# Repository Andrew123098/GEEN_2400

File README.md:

# EngineeringForTheCommunity

A Particle project named EngineeringForTheCommunity

## Welcome to your project!

Every new Particle project is composed of 3 important elements that you'll see have been created in your project directory for EngineeringForTheCommunity.

#### ```/src``` folder:  
This is the source folder that contains the firmware files for your project. It should *not* be renamed. 
Anything that is in this folder when you compile your project will be sent to our compile service and compiled into a firmware binary for the Particle device that you have targeted.

If your application contains multiple files, they should all be included in the `src` folder. If your firmware depends on Particle libraries, those dependencies are specified in the `project.properties` file referenced below.

#### ```.ino``` file:
This file is the firmware that will run as the primary application on your Particle device. It contains a `setup()` and `loop()` function, and can be written in Wiring or C/C++. For more information about using the Particle firmware API to create firmware for your Particle device, refer to the [Firmware Reference](https://docs.particle.io/reference/firmware/) section of the Particle documentation.

#### ```project.properties``` file:  
This is the file that specifies the name and version number of the libraries that your project depends on. Dependencies are added automatically to your `project.properties` file when you add a library to a project using the `particle library add` command in the CLI or add a library in the Desktop IDE.

## Adding additional files to your project

#### Projects with multiple sources
If you would like add additional files to your application, they should be added to the `/src` folder. All files in the `/src` folder will be sent to the Particle Cloud to produce a compiled binary.

#### Projects with external libraries
If your project includes a library that has not been registered in the Particle libraries system, you should create a new folder named `/lib/<libraryname>/src` under `/<project dir>` and add the `.h` and `.cpp` files for your library there. All contents of the `/lib` folder and subfolders will also be sent to the Cloud for compilation.

## Compiling your project

When you're ready to compile your project, make sure you have the correct Particle device target selected and run `particle compile <platform>` in the CLI or click the Compile button in the Desktop IDE. The following files in your project folder will be sent to the compile service:

- Everything in the `/src` folder, including your `.ino` application file
- The `project.properties` file for your project
- Any libraries stored under `lib/<libraryname>/src`# GEEN_2400

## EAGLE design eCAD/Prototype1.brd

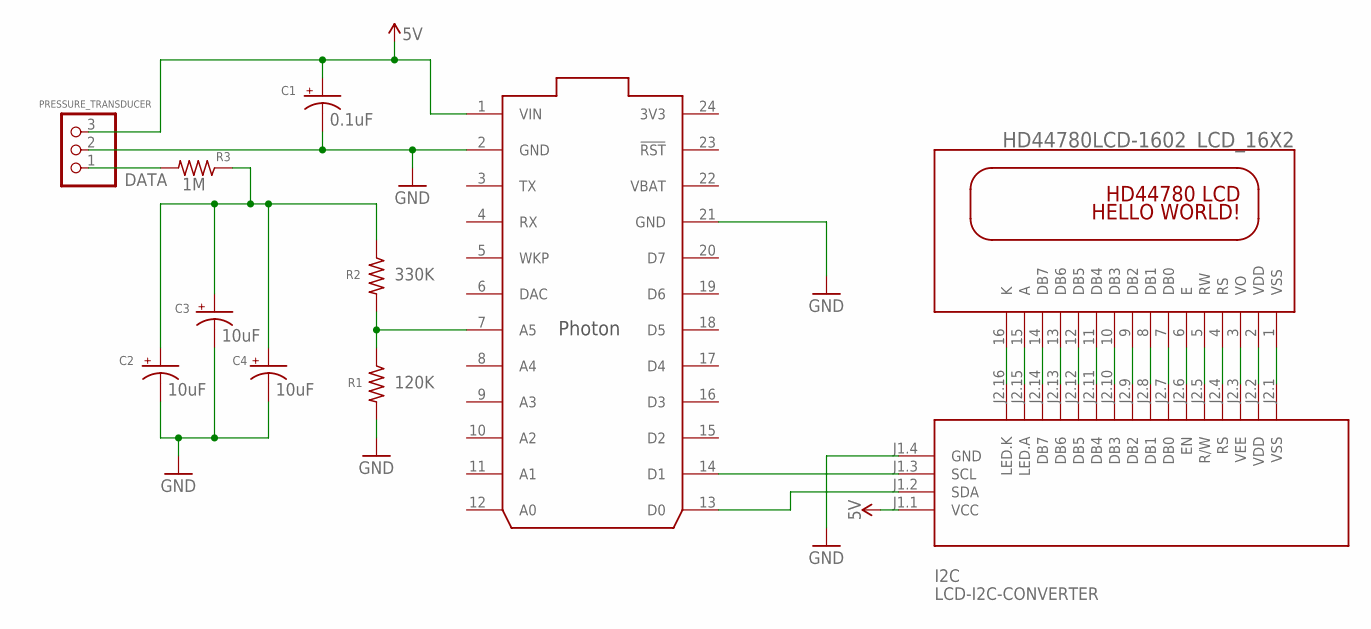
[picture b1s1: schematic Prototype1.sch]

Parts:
C1: 0.1uF; E2,5-7
C2, C3, C4: 10uF; E2,5-5
I2C: LCD-I2C-CONVERTER
LCD_16X2: HD44780LCD-1602; LCD1602
PHOTON: PHOTON_WITH_HEADERS; PHOTON
PRESSURE_TRANSDUCER: PINHD-1X3; 1X03
R1: 120K; 0207/10
R2: 330K; 0207/10
R3: 1M; 0207/10

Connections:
3V3: PHOTON.24 (3V3)
5V: C1.+, I2C.J1.1 (VCC), PHOTON.1 (VIN), PRESSURE_TRANSDUCER.3
DATA: C2.+, C3.+, C4.+, R2.1, R3.1
GND: C1.-, C2.-, C3.-, C4.-, I2C.J1.4 (GND), PHOTON.2 (GND), PHOTON.21 (GND), PRESSURE_TRANSDUCER.2, R1.2
unnamed: PHOTON.7 (A5), R1.1, R2.2
unnamed: I2C.J2.4 (RS), I2C.J2.14 (DB7), LCD_16X2.4 (RS), LCD_16X2.14 (DB7)
unnamed: I2C.J2.5 (R/W), I2C.J2.15 (LED.A), LCD_16X2.5 (RW), LCD_16X2.15 (A)
unnamed: I2C.J2.3 (VEE), LCD_16X2.3 (VO)
unnamed: I2C.J2.7 (DB0), LCD_16X2.7 (DB0)
unnamed: I2C.J2.8 (DB1), LCD_16X2.8 (DB1)
unnamed: I2C.J2.9 (DB2), LCD_16X2.9 (DB2)
unnamed: I2C.J2.10 (DB3), LCD_16X2.10 (DB3)
unnamed: I2C.J2.11 (DB4), LCD_16X2.11 (DB4)
unnamed: I2C.J2.12 (DB5), LCD_16X2.12 (DB5)
unnamed: I2C.J2.13 (DB6), LCD_16X2.13 (DB6)
unnamed: I2C.J2.16 (LED.K), LCD_16X2.16 (K)
unnamed: I2C.J2.6 (EN), LCD_16X2.6 (E)
unnamed: I2C.J1.2 (SDA), PHOTON.13 (D0)
unnamed: I2C.J1.3 (SCL), PHOTON.14 (D1)
unnamed: PRESSURE_TRANSDUCER.1, R3.2
VBAT: PHOTON.22 (VBAT)
VDD: I2C.J2.2 (VDD), LCD_16X2.2 (VDD)
VSS: I2C.J2.1 (VSS), LCD_16X2.1 (VSS)

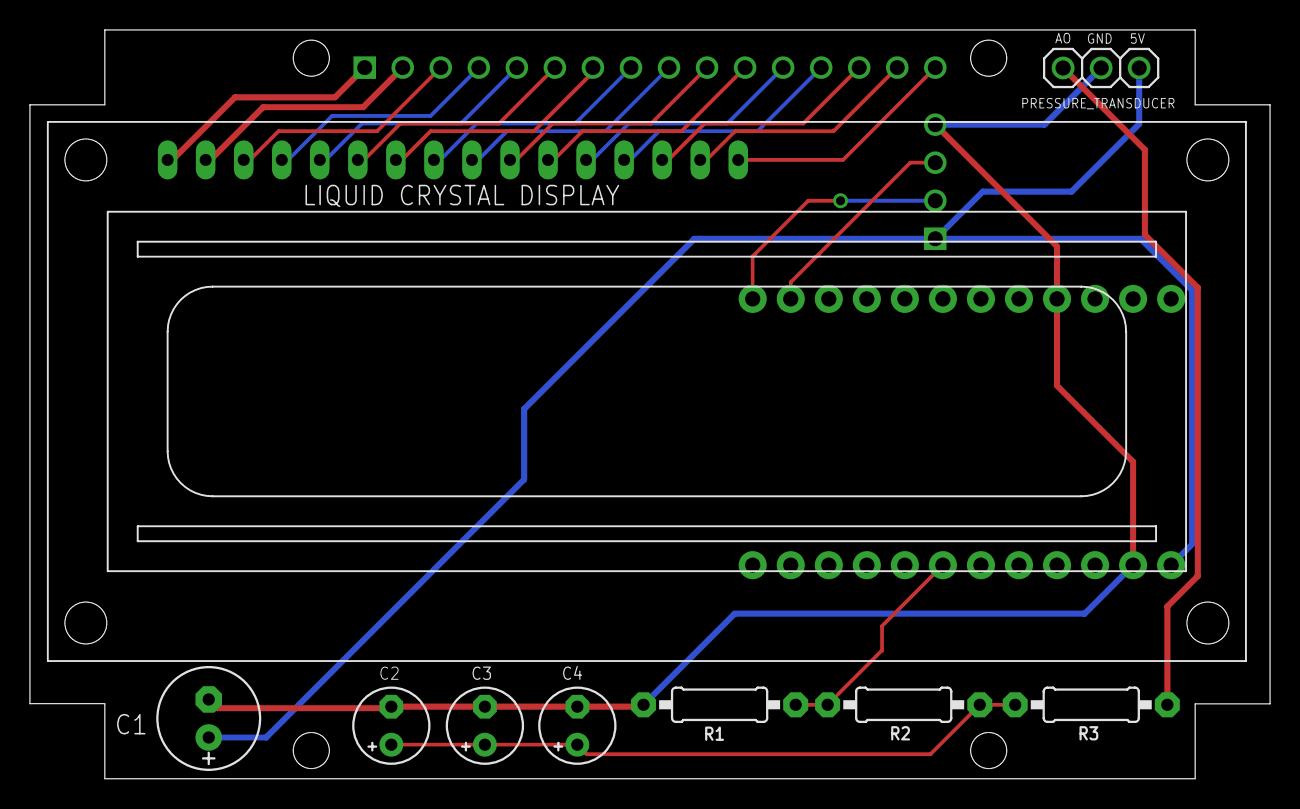
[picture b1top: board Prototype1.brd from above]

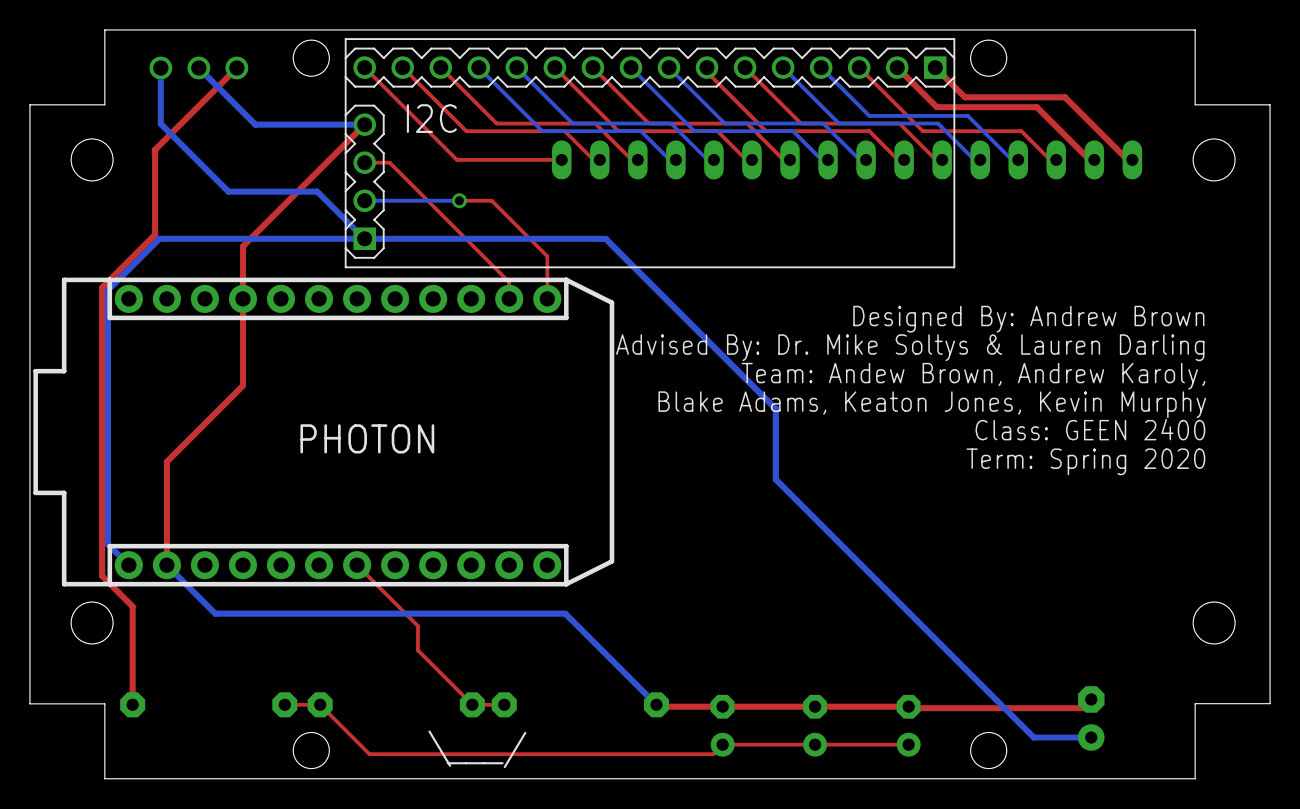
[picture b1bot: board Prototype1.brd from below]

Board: 2 copper layers, 82.8 x 50.0 mm, 11 parts (2 on the bottom side), 21 nets.

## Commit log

2020-05-03 Add eCAD
2020-05-03 Add CAD Files
2020-05-18 still some issues with checkTimeAndPressure function
2020-05-18 need to fix file structure for multiple calls of setup and loop error
2020-07-06 Fixed build tree
2020-07-09 Visual Studio Code is working. LCD is source of firmware crashing
2020-07-09 File tree fix

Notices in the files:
parts and their libraries:
diy-modules: Released under the Creative Commons Attribution 4.0 International License: http://creativecommons.org/licenses/by/4.0
Particle-Devices: Licensing: Designed by Particle.
